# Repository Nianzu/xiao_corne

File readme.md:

https://docs.espressif.com/projects/rust/book/getting-started/toolchain.html
# Toolchain
```
sudo apt install build-essential
cargo install espup --locked 
espup install
cat $HOME/export-esp.sh >> ~/.bashrc
```
# Tooling
```
cargo install esp-generate --locked
cargo install espflash --locked
cargo install esp-config --features=tui --locked
```

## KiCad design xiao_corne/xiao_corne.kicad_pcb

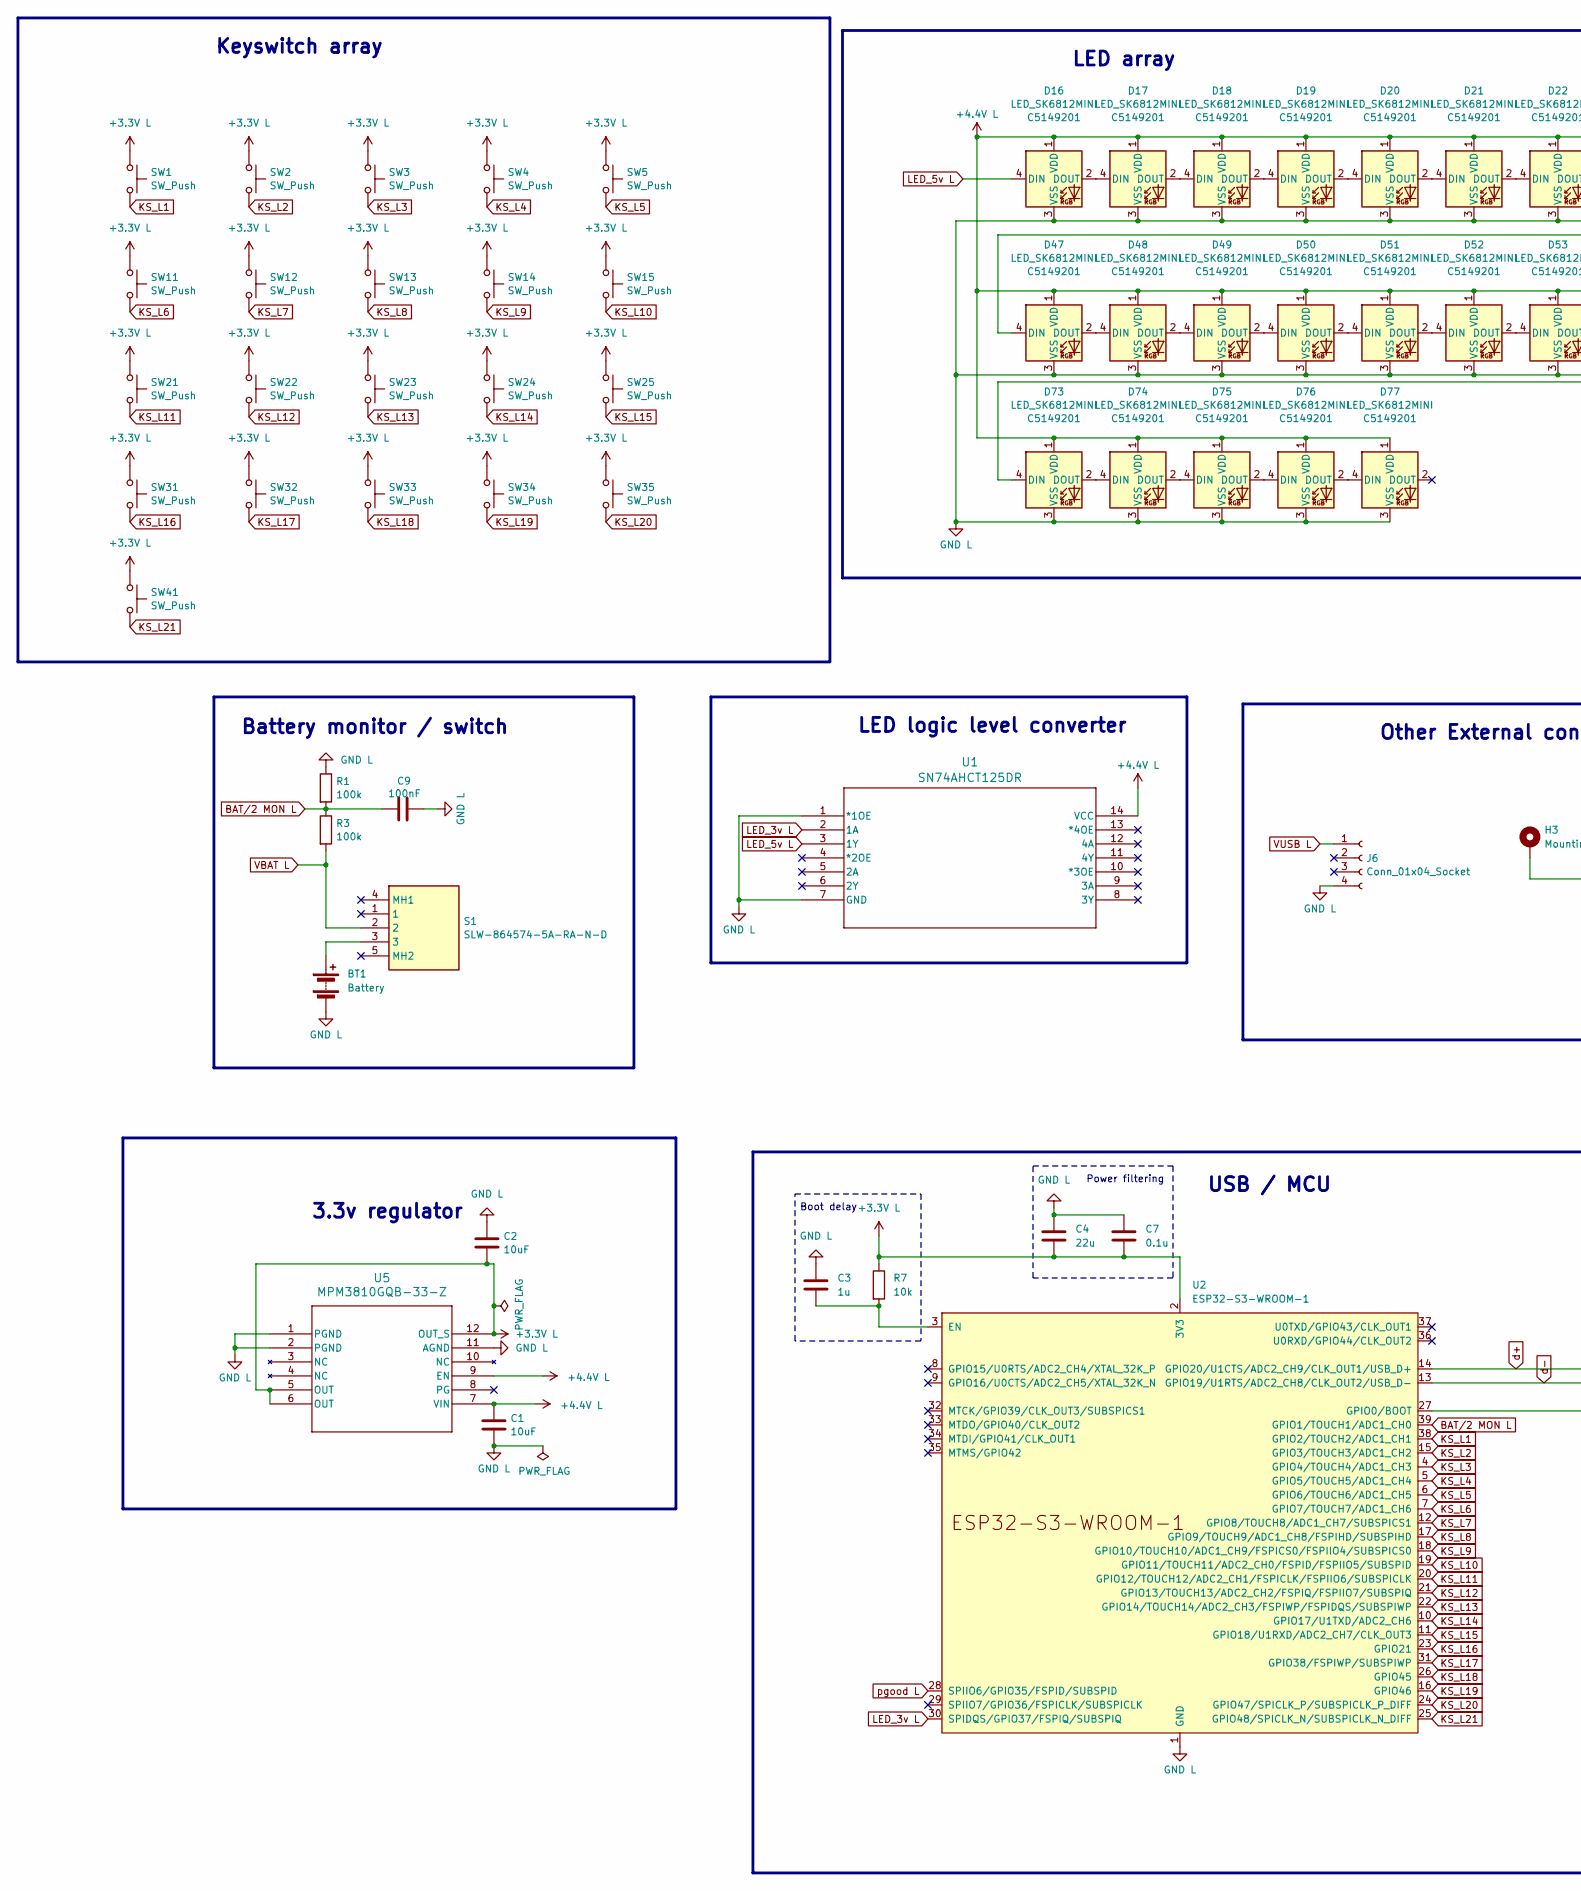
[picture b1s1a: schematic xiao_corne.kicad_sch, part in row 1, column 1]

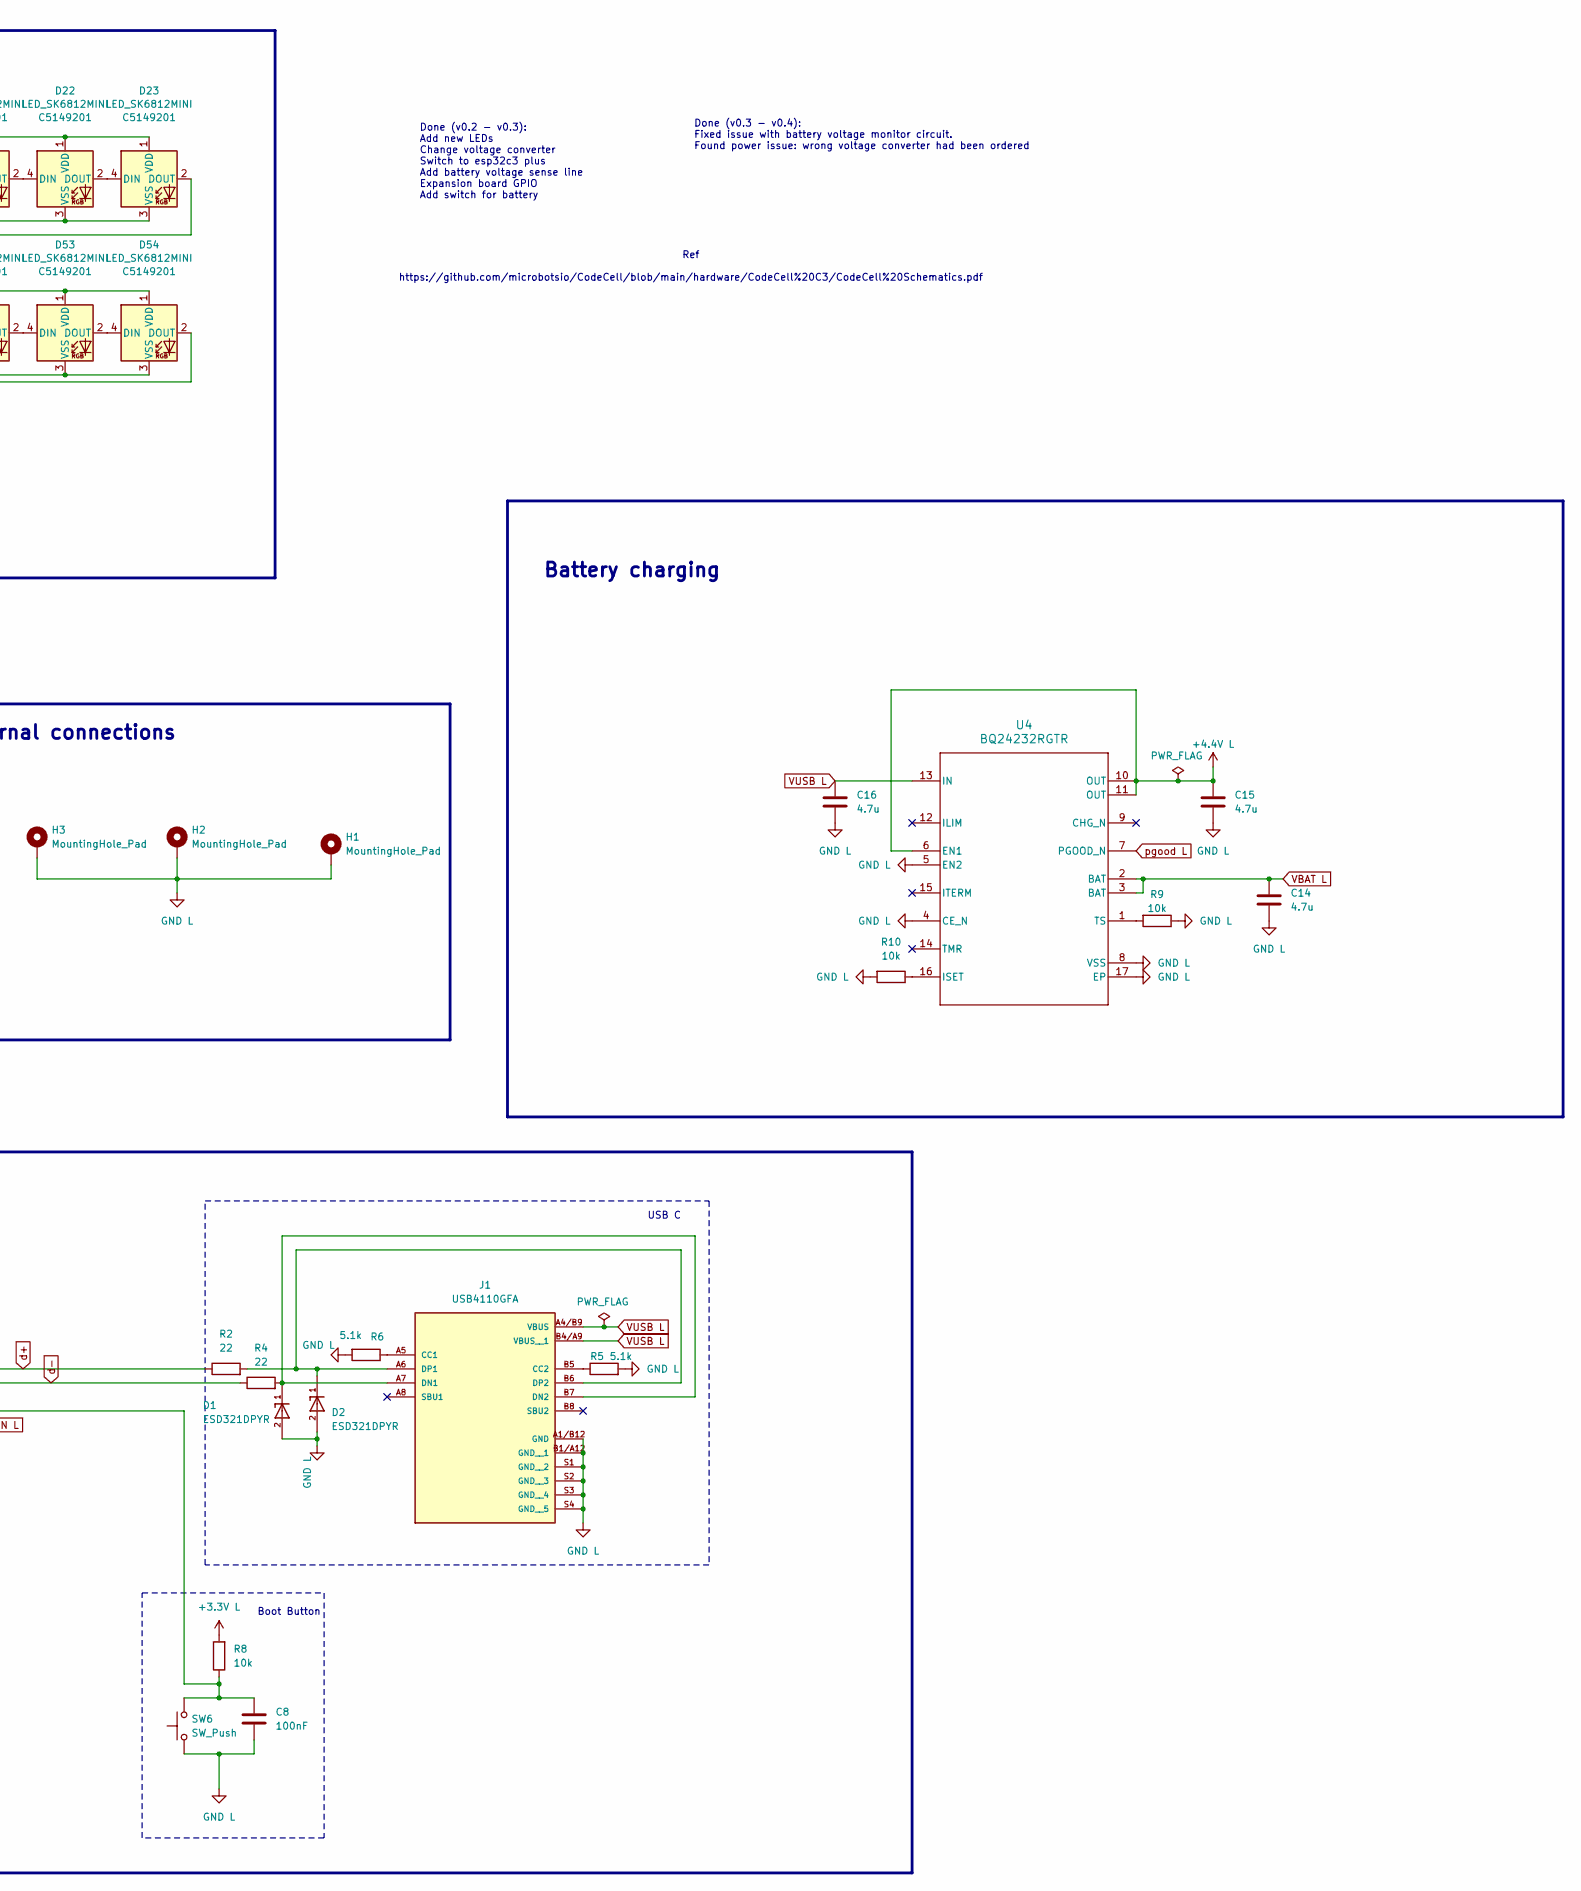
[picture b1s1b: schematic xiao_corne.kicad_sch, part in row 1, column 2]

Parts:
BT1: Battery; PinHeader_1x02_P2.00mm_Vertical
C1, C2: 10uF; C_0805_2012Metric
C3: 1u; C_0805_2012Metric
C4: 22u; C_0805_2012Metric
C7: 0.1u; C_0805_2012Metric
C8, C9: 100nF; C_0805_2012Metric
C14, C15, C16: 4.7u; C_0805_2012Metric
D1, D2: ESD321DPYR; TVS_ESD321DPYR; PARTREV B
D16, D17, D18, D19, D20, D21, D22, D23, D47, D48, D49, D50, D51, D52, D53, D54, D73, D74, D75, D76, D77: LED_SK6812MINI; LCSC C5149201
H1, H2, H3: MountingHole_Pad; MountingHole_2.2mm_M2_ISO14580_Pad_TopBottom
J1: USB4110GFA; GCT_USB4110GFA
J6: Conn_01x04_Socket; PinHeader_1x04_P2.54mm_Vertical
R1, R3: 100k; R_0805_2012Metric
R2, R4: 22; R_0805_2012Metric
R5, R6: 5.1k; R_0805_2012Metric
R7, R8, R9, R10: 10k; R_0805_2012Metric
S1: SLW-864574-5A-RA-N-D; SW_SLW-864574-5A-RA-N-D; Mouser Part Number 179-SLW8645745ARAND
SW1, SW2, SW3, SW4, SW5, SW11, SW12, SW13, SW14, SW15, SW21, SW22, SW23, SW24, SW25, SW31, SW32, SW33, SW34, SW35, SW41: SW_Push; Hotswap_Choc_V1V2
SW6: SW_Push; MJTP1117
U1: SN74AHCT125DR; D14
U2: ESP32-S3-WROOM-1
U4: BQ24232RGTR; RGT0016C
U5: MPM3810GQB-33-Z; QFN-12_MPM3810_MNP

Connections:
+3.3V L: C2.1, C4.2, C7.2, R7.1, R8.2, SW1.1, SW2.1, SW3.1, SW4.1, SW5.1, SW11.1, SW12.1, SW13.1, SW14.1, SW15.1, SW21.1, SW22.1, SW23.1, SW24.1, SW25.1, SW31.1, SW32.1, SW33.1, SW34.1, SW35.1, SW41.1, U2.2 (3V3), U5.5 (OUT), U5.6 (OUT), U5.12 (OUT_S)
+4.4V L: C1.2, C15.1, D16.1 (VDD), D17.1 (VDD), D18.1 (VDD), D19.1 (VDD), D20.1 (VDD), D21.1 (VDD), D22.1 (VDD), D23.1 (VDD), D47.1 (VDD), D48.1 (VDD), D49.1 (VDD), D50.1 (VDD), D51.1 (VDD), D52.1 (VDD), D53.1 (VDD), D54.1 (VDD), D73.1 (VDD), D74.1 (VDD), D75.1 (VDD), D76.1 (VDD), D77.1 (VDD), U1.14 (VCC), U4.6 (EN1), U4.10 (OUT), U4.11 (OUT), U5.7 (VIN), U5.9 (EN)
BAT/2 MON L: C9.2, R1.2, R3.1, U2.39 (GPIO1/TOUCH1/ADC1_CH0)
GND L: BT1.2 (-), C1.1, C2.2, C3.1, C4.1, C7.1, C8.2, C9.1, C14.2, C15.2, C16.2, D1.2, D2.2, D16.3 (VSS), D17.3 (VSS), D18.3 (VSS), D19.3 (VSS), D20.3 (VSS), D21.3 (VSS), D22.3 (VSS), D23.3 (VSS), D47.3 (VSS), D48.3 (VSS), D49.3 (VSS), D50.3 (VSS), D51.3 (VSS), D52.3 (VSS), D53.3 (VSS), D54.3 (VSS), D73.3 (VSS), D74.3 (VSS), D75.3 (VSS), D76.3 (VSS), D77.3 (VSS), H1.1 (1_1), H2.1 (1_1), H3.1 (1_1), J1.A1/B12 (GND), J1.B1/A12 (GND__1), J1.S1 (GND__2), J1.S2 (GND__3), J1.S3 (GND__4), J1.S4 (GND__5), J6.4, R1.1, R5.2, R6.2, R9.1, R10.2, SW6.1, U1.1 (*1OE), U1.7 (GND), U2.1 (GND), U2.40 (GND), U2.41 (GND), U4.4 (CE_N), U4.5 (EN2), U4.8 (VSS), U4.17 (EP), U4.V, U5.1 (PGND), U5.2 (PGND), U5.11 (AGND)
KS_L1: SW1.2, U2.38 (GPIO2/TOUCH2/ADC1_CH1)
KS_L2: SW2.2, U2.15 (GPIO3/TOUCH3/ADC1_CH2)
KS_L3: SW3.2, U2.4 (GPIO4/TOUCH4/ADC1_CH3)
KS_L4: SW4.2, U2.5 (GPIO5/TOUCH5/ADC1_CH4)
KS_L5: SW5.2, U2.6 (GPIO6/TOUCH6/ADC1_CH5)
KS_L6: SW11.2, U2.7 (GPIO7/TOUCH7/ADC1_CH6)
KS_L7: SW12.2, U2.12 (GPIO8/TOUCH8/ADC1_CH7/SUBSPICS1)
KS_L8: SW13.2, U2.17 (GPIO9/TOUCH9/ADC1_CH8/FSPIHD/SUBSPIHD)
KS_L9: SW14.2, U2.18 (GPIO10/TOUCH10/ADC1_CH9/FSPICS0/FSPIIO4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)
KS_L10: SW15.2, U2.19 (GPIO11/TOUCH11/ADC2_CH0/FSPID/FSPIIO5/S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)
KS_L11: SW21.2, U2.20 (GPIO12/TOUCH12/ADC2_CH1/FSPICLK/FSPIIO6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)
KS_L12: SW22.2, U2.21 (GPIO13/TOUCH13/ADC2_CH2/FSPIQ/FSPIIO7/S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)
KS_L13: SW23.2, U2.22 (GPIO14/TOUCH14/ADC2_CH3/FSPIWP/FSPIDQS/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)
KS_L14: SW24.2, U2.10 (GPIO17/U1TXD/ADC2_CH6)
KS_L15: SW25.2, U2.11 (GPIO18/U1RXD/ADC2_CH7/CLK_OUT3)
KS_L16: SW31.2, U2.23 (GPIO21)
KS_L17: SW32.2, U2.31 (GPIO38/FSPIWP/SUBSPIWP)
KS_L18: SW33.2, U2.26 (GPIO45)
KS_L19: SW34.2, U2.16 (GPIO46)
KS_L20: SW35.2, U2.24 (GPIO47/SPICLK_P/SUBSPICLK_P_DIFF)
KS_L21: SW41.2, U2.25 (GPIO48/SPICLK_N/SUBSPICLK_N_DIFF)
LED_3v L: U1.2 (1A), U2.30 (SPIDQS/GPIO37/FSPIQ/SUBSPIQ)
LED_5v L: D16.4 (DIN), U1.3 (1Y)
unnamed: BT1.1 (+), S1.3
unnamed: D16.2 (DOUT), D17.4 (DIN)
unnamed: D17.2 (DOUT), D18.4 (DIN)
unnamed: D18.2 (DOUT), D19.4 (DIN)
unnamed: D19.2 (DOUT), D20.4 (DIN)
unnamed: D20.2 (DOUT), D21.4 (DIN)
unnamed: D21.2 (DOUT), D22.4 (DIN)
unnamed: D22.2 (DOUT), D23.4 (DIN)
unnamed: D23.2 (DOUT), D47.4 (DIN)
unnamed: D47.2 (DOUT), D48.4 (DIN)
unnamed: D48.2 (DOUT), D49.4 (DIN)
unnamed: D49.2 (DOUT), D50.4 (DIN)
unnamed: D50.2 (DOUT), D51.4 (DIN)
unnamed: D51.2 (DOUT), D52.4 (DIN)
unnamed: D52.2 (DOUT), D53.4 (DIN)
unnamed: D53.2 (DOUT), D54.4 (DIN)
unnamed: D54.2 (DOUT), D73.4 (DIN)
unnamed: D73.2 (DOUT), D74.4 (DIN)
unnamed: D74.2 (DOUT), D75.4 (DIN)
unnamed: D75.2 (DOUT), D76.4 (DIN)
unnamed: D76.2 (DOUT), D77.4 (DIN)
unnamed: J1.A5 (CC1), R6.1
unnamed: J1.B5 (CC2), R5.1
unnamed: D1.1, J1.A7 (DN1), J1.B7 (DN2), R4.2
unnamed: D2.1, J1.A6 (DP1), J1.B6 (DP2), R2.2
unnamed: C3.2, R7.2, U2.3 (EN)
unnamed: C8.1, R8.1, SW6.2, U2.27 (GPIO0/BOOT)
unnamed: R10.1, U4.16 (ISET)
unnamed: R9.2, U4.1 (TS)
VBAT L: C14.1, R3.2, S1.2, U4.2 (BAT), U4.3 (BAT)
VUSB L: C16.1, J1.A4/B9 (VBUS), J1.B4/A9 (VBUS__1), J6.1, U4.13 (IN)
d+: R2.1, U2.14 (GPIO20/U1CTS/ADC2_CH9/CLK_OUT1/USB_D+)
d-: R4.1, U2.13 (GPIO19/U1RTS/ADC2_CH8/CLK_OUT2/USB_D-)
pgood L: U2.28 (SPIIO6/GPIO35/FSPID/SUBSPID), U4.7 (PGOOD_N)

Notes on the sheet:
USB / MCU
Battery charging
USB C
Boot Button
Battery monitor / switch
Keyswitch array
Done (v0.2 - v0.3): Add new LEDs Change voltage converter Switch to esp32c3 plus Add battery voltage sense line Expansion board GPIO Add switch for battery
Boot delay
LED logic level converter
LED array
3.3v regulator
Other External connections
Power filtering
Ref https://github.com/microbotsio/CodeCell/blob/main/hardware/CodeCell%20C3/CodeCell%20Schematics.pdf
Done (v0.3 - v0.4): Fixed issue with battery voltage monitor circuit. Found power issue: wrong voltage converter had been ordered

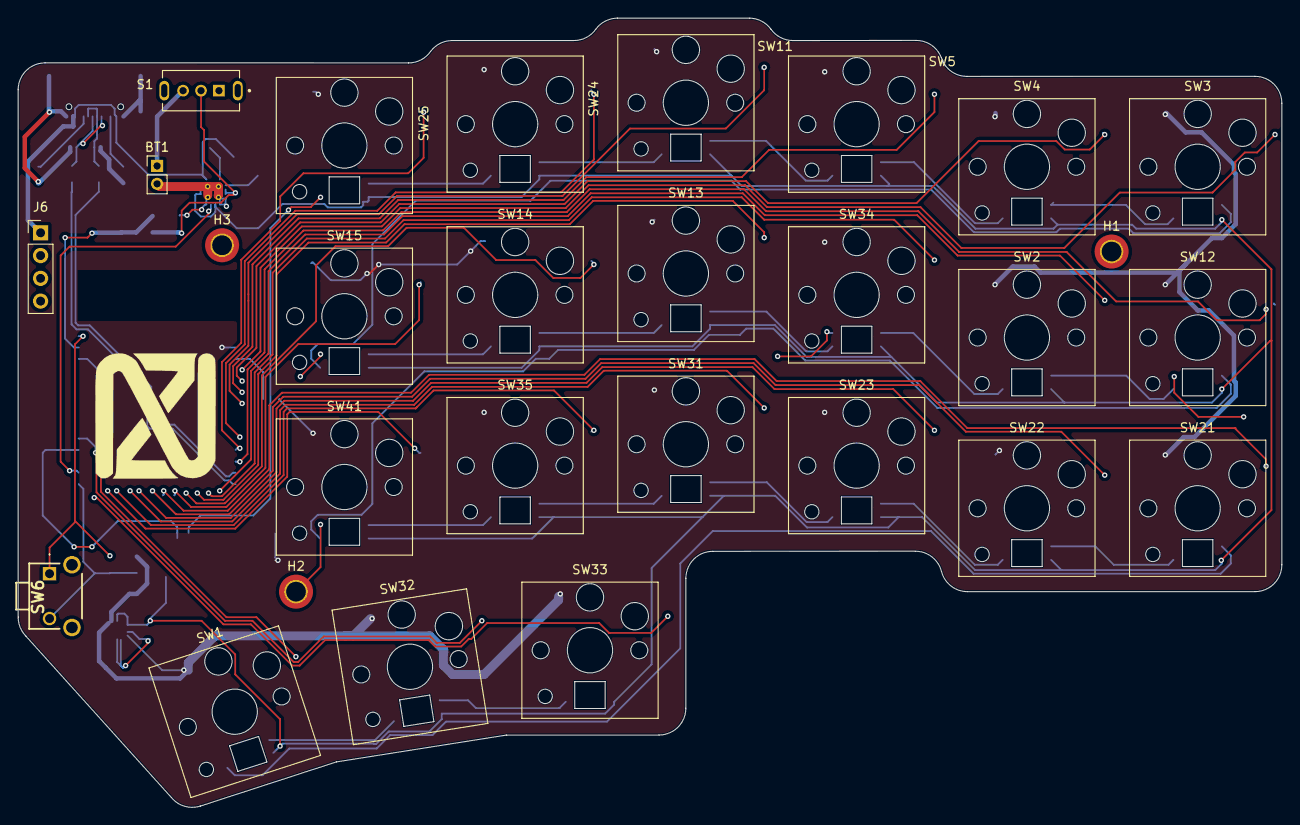
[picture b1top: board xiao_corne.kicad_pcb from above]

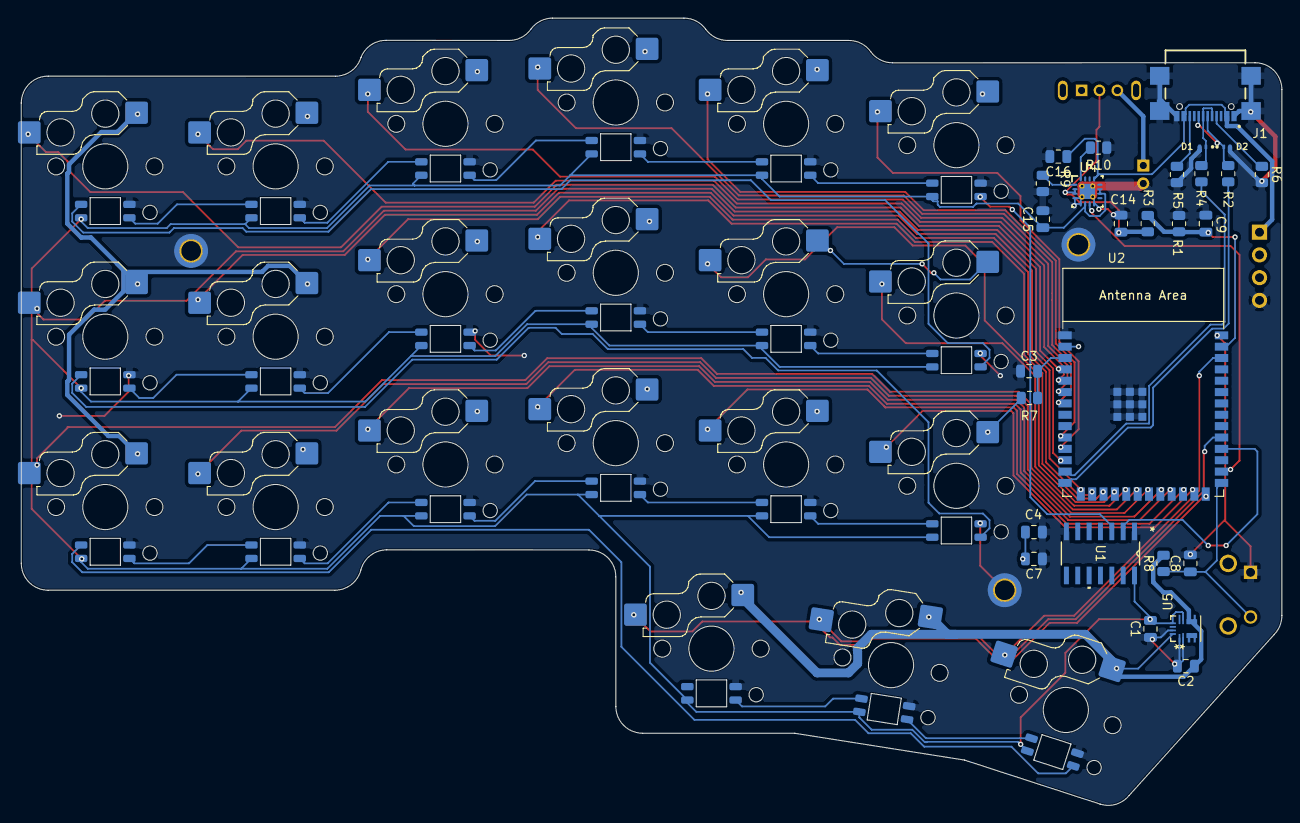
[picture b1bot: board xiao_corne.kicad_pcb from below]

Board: 2 copper layers, 140.9 x 88.0 mm, 76 parts (48 on the bottom side), 61 nets.

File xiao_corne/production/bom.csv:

Designator,Footprint,Quantity,Value,LCSC Part #
BT1,PinHeader_1x02_P2.00mm_Vertical,1,Battery,
"C1, C2",0805,2,10uF,
"C14, C15, C16",0805,3,4.7u,
C3,0805,1,1u,
C4,0805,1,22u,
C7,0805,1,0.1u,
"C8, C9",0805,2,100nF,
"D1, D2",TVS_ESD321DPYR,2,ESD321DPYR,
"D16, D17, D18, D19, D20, D21, D22, D23, D47, D48, D49, D50, D51, D52, D53, D54, D73, D74, D75, D76, D77",LED_SK6812MINI,21,LED_SK6812MINI,C5149201
J1,GCT_USB4110GFA,1,USB4110GFA,
J6,PinHeader_1x04_P2.54mm_Vertical,1,Conn_01x04_Socket,
"R1, R3",0805,2,100k,
"R10, R7, R8, R9",0805,4,10k,
"R2, R4",0805,2,22,
"R5, R6",0805,2,5.1k,
S1,SW_SLW-864574-5A-RA-N-D,1,SLW-864574-5A-RA-N-D,
"SW1, SW11, SW12, SW13, SW14, SW15, SW2, SW21, SW22, SW23, SW24, SW25, SW3, SW31, SW32, SW33, SW34, SW35, SW4, SW41, SW5",Hotswap_Choc_V1V2,21,SW_Push,
SW6,MJTP1117,1,SW_Push,
U1,D14,1,SN74AHCT125DR,
U2,ESP32-S3-WROOM-1,1,ESP32-S3-WROOM-1,
U4,RGT0016C,1,BQ24232RGTR,
U5,QFN-12_MPM3810_MNP,1,MPM3810GQB-33-Z,

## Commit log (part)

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2025-03-23 first production test
2025-03-30 Hardware V0.2
2025-04-17 Ordered V0.2, programmed it to output numbers
2025-05-07 Added keymaps for left and right sides
2025-05-07 Sorta typing in a bad and backwards way
2025-05-08 Left half keyboard basic fully working, minus LEDs
2025-05-08 LEDs working. So many wasted hours, because the adafruit library broke after 1.12.3.........
2025-05-08 Fully working for both left and right sides individualy, with LEDs!
2025-05-08 Formatting pass
2025-05-08 I wrote this commit message with my now fully functional keyboard. LEDs and all
2025-05-09 Added support for up to 5 layers!
2025-05-09 Removed serial port, added key release on layer switch
2025-05-10 Added left half gaming layer
2025-05-10 Added backup from order
2025-05-15 Set LEDs to batch update.
2025-05-16 Significant refactor to support macros in the future.
2025-05-16 Split layouts and types into own files.
2025-05-16 migrate esp code to own file
2025-05-16 Revert "migrate esp code to own file"
    This reverts commit 80cdbd023e9a3cd406f6e0397eed5206af872bd4.
2025-05-16 Fix but with definitions out of order
2025-05-16 LED layer functionality added for left side!
2025-05-16 Added LED map to right side, fixed overwritting issue
2025-07-20 Major work for update to 0.3!
2025-07-20 Production files for v0.3
2025-07-22 Added 3d models for pretty much everything
2025-07-22 increased heat via size to be manufactureable
2025-07-22 Created manufacturing files to reflect change
2025-11-15 Fixed issue with battery voltage monitor
2026-01-19 Found some issues with the PCB, updated layout
2026-01-21 Added basic readme, rust stuff
2026-01-21 Auto-generated rust boilerplate for esp32s3. Printing hello world!
2026-01-21 Another try, this time using esp-idf (not no-std). Auto generated boilerplate
2026-02-11 WIP large upgrade to keyboard design
2026-02-16 Finished sketch of schematic
2026-02-23 starting layout for left side
2026-02-25 almost done routing left half!
2026-02-26 ready for review
2026-02-27 changed 3.3v regulator to step down from step up converter
2026-03-03 ordered!
2026-03-31 Fixed issue with battery monitor
2026-04-02 got right side components flipped and generally correct
2026-04-11 right PCB ready for final review!
2026-04-15 Right side ordered!
